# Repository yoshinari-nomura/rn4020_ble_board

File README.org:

#+TITLE: RN4020 を使った iBeacon 作成
#+AUTHOR: 乃村 能成
#+EMAIL:
#+DATE: 2017-06-30
#+OPTIONS: H:3 num:2 toc:nil
#+OPTIONS: ^:nil @:t \n:nil ::t |:t f:t TeX:t
#+OPTIONS: skip:nil
#+OPTIONS: author:t
#+OPTIONS: email:nil
#+OPTIONS: creator:nil
#+OPTIONS: timestamp:nil
#+OPTIONS: timestamps:nil
#+OPTIONS: d:nil
#+OPTIONS: tags:t
#+TEXT:
#+DESCRIPTION:
#+KEYWORDS:
#+LANGUAGE: ja
#+LATEX_CLASS: jsarticle
#+LATEX_CLASS_OPTIONS: [a4j,dvipdfmx]
# #+LATEX_HEADER: \usepackage{plain-article}
# #+LATEX_HEADER: \renewcommand\maketitle{}
# #+LATEX_HEADER: \pagestyle{empty}
# #+LaTeX: \thispagestyle{empty}

[[file:images/rn4020_ble_board1s.jpg]]
[[file:images/rn4020_ble_board2s.jpg]]

* はじめに
  Microchip の RN4020 は，Bluetooth Low Energy 機器作成に必要な機能を1チップに収めた
  非常に使いやすいマイコン製品です．以下の特徴があります．

  + 消費電力非常に小さい
  + 簡易的ながら柔軟なユーザスクリプトを記述できる
  + 特別な開発環境(コンパイラ)の整備が不要

* ディレクトリ構成
  + file:TECHNICAL-MEMO.org :: 作成時に気付いたことなどのメモやノウハウ
  + file:README.org :: このファイル
  + file:datasheet/ :: RN4020 のデータシート
  + file:images/ :: 回路図(PDF)，CADの3Dイメージ，設置例写真など
  + file:kicad/ :: 回路図，基板作成CADのデータ
    + file:garber/ :: PCB注文時のzipファイルと作成用シェルスクリプトなど
  + file:rn4020_scripts/ :: RN4020に書込むユーザスクリプト例

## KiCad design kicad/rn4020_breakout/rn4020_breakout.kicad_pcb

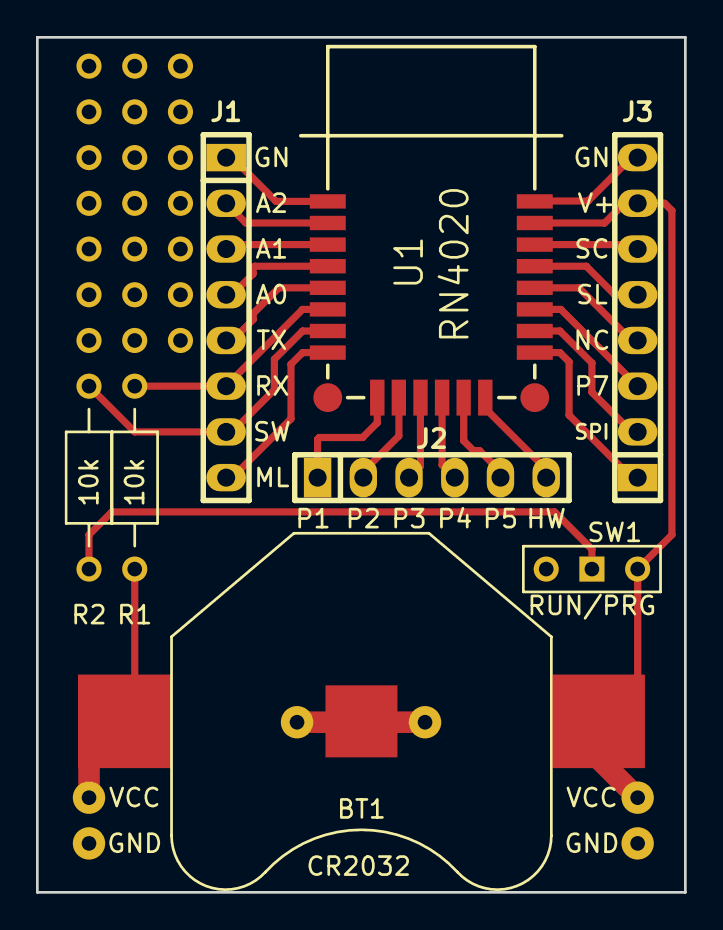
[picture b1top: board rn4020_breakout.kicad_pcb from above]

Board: 2 copper layers, 36.0 x 47.5 mm, 8 parts (0 on the bottom side), 22 nets.

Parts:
BT1: CR2032; BC-2001
J1, J3: HEADER_8; pin_socket_8
J2: HEADER_6; pin_socket_6
R1, R2: 10k; Resistor_Horizontal_RM10mm
SW1: RUN/PRG; SW_Micro_SPDT
U1: RN4020

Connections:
GND: BT1.2, J1.1, J3.8, SW1.3, U1.1, U1.24
unnamed: J1.2, U1.2
unnamed: J1.3, U1.3
unnamed: J1.4, U1.4
unnamed: J1.5, U1.5
unnamed: J1.6, R1.2, U1.6
unnamed: J1.7, R2.1, U1.7
unnamed: J1.8, U1.8
unnamed: J2.1, U1.10
unnamed: J2.2, U1.11
unnamed: J2.3, U1.12
unnamed: J2.4, U1.13
unnamed: J2.5, U1.14
unnamed: J2.6, U1.15
unnamed: J3.1, U1.17
unnamed: J3.2, U1.18
unnamed: J3.3, U1.19
unnamed: J3.4, U1.20
unnamed: J3.5, U1.21
unnamed: J3.6, U1.22
unnamed: R2.2, SW1.1
VCC: BT1.1, J3.7, R1.1, SW1.2, U1.23

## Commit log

2018-06-29 Fix typo
2018-06-29 Add TECHNICAL-MEMO.org
2018-06-29 Add pictures to README
